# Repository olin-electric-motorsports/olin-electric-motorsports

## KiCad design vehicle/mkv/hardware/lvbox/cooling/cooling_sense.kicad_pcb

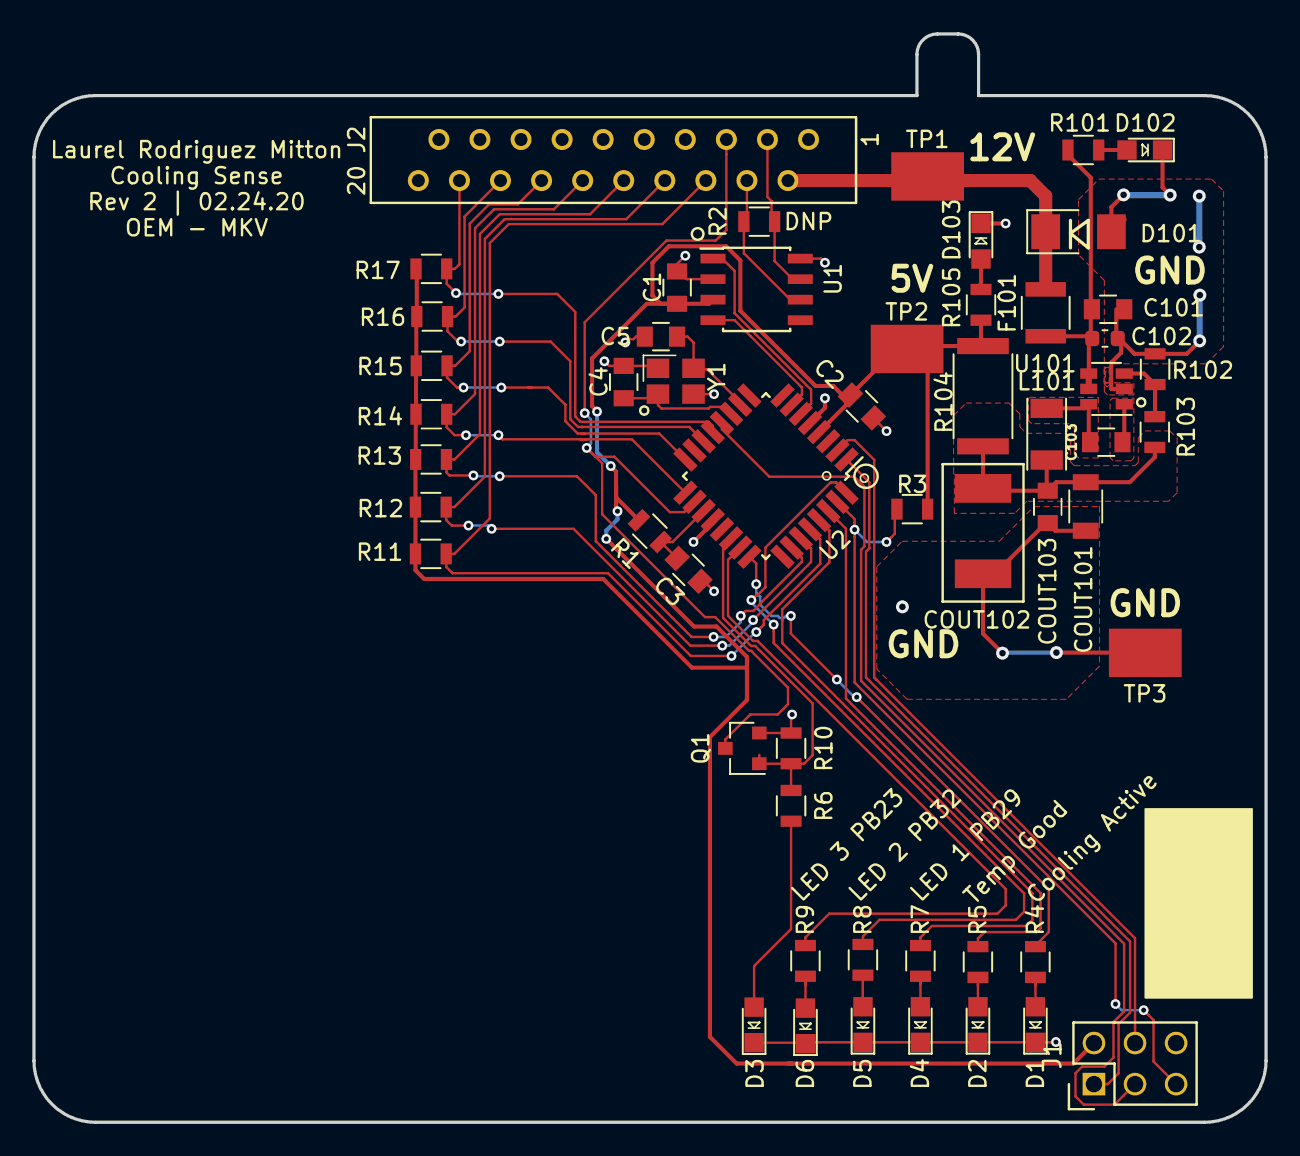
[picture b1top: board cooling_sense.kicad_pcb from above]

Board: 2 copper layers, 76.2 x 67.3 mm, 54 parts (0 on the bottom side), 41 nets.

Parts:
C1, C2, C101, C103: C_0.1uF; C_0805_OEM
C3: C_100pF; C_0805_OEM
C4, C5: C_30pF; C_0805_OEM
C102: C_2.2uF; C_0603_1608Metric
COUT101: C_22uF; C_1206_OEM
COUT102: C_33uF; Fuse_1812
COUT103: C_47uF; C_0805_OEM
D1, D2, D3, D4, D5, D6, D102, D103: LED_0805; LED_0805_OEM
D101: D_Zener_18V; DO-214AA
F101: F_500mA_16V; Fuse_1210
J1: CONN_02X03; Pin_Header_Straight_2x03
J2: MM_F_RA_20; micromatch_female_ra_20
L101: L_100uH; L_100uH_OEM
Q1: SSM3K333R; SOT-23F
R1: R_100; R_0805_OEM
R2: R_120_DNP; R_0805_OEM
R3, R10, R11, R12, R13, R14, R15, R16, R17: R_10K; R_0805_OEM
R4, R5, R6, R7, R8, R9, R101, R105: R_200; R_0805_OEM
R102: R_25K; R_0805_OEM
R103: R_100K; R_0805_OEM
R104: R_0_2512; R_2512_OEM
TP1, TP2, TP3: Test_Point_SMD
U1: MCP2561-E_SN; SOIC-8_3.9x4.9mm_Pitch1.27mm_OEM
U2: ATMEGA16M1; TQFP-32_7x7mm_Pitch0.8mm
U101: TPS560430YF; SOT-23-6_OEM
Y1: Crystal_SMD; Crystal_SMD_FA238

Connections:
/12V: D101.1, F101.2, J2.2, TP1.1
/CAN_HI: J2.3, R2.1, U1.7
/CAN_LO: J2.4, R2.2, U1.6
/CAN_RX: U1.4, U2.7
/CAN_TX: U1.1, U2.6
/COOLING_ACTIVE_LED: R4.1, U2.24
/LED_1: R7.1, U2.29
/LED_2: R8.1, U2.32
/LED_3: R9.1, U2.23
/MISO: J1.1, U2.1
/MOSI: J1.4, U2.2
/PUMP_CONTROL: Q1.1, R6.2, R10.2, U2.22
/PUMP_RELAY_READ: J2.5, Q1.3, U2.18
/READ_1: J2.6, R11.2, U2.28
/READ_2: J2.8, R12.2, U2.27
/READ_3: J2.10, R13.2, U2.26
/READ_4: J2.12, R14.2, U2.17
/READ_5: J2.14, R15.2, U2.16
/READ_6: J2.16, R16.2, U2.14
/READ_7: J2.18, R17.2, U2.13
/RESET: J1.5, R3.2, U2.31
/SCK: J1.3, U2.12
/TEMP_GOOD_LED: R5.1, U2.30
GND: C1.2, C2.2, C3.2, C4.2, C5.2, C101.2, C102.2, COUT101.2, COUT102.2, COUT103.2, D1.1, D2.1, D3.1, D4.1, D5.1, D6.1, D101.2, D102.1, D103.1, J1.6, J2.1, J2.7, J2.9, J2.11, J2.13, J2.15, J2.17, J2.19, J2.20, Q1.2, R10.1, R102.2, TP3.1, U1.2, U1.8, U2.5, U2.20, U101.2, Y1.2, Y1.4
unnamed: C3.1, R1.2, U2.19
unnamed: C4.1, U2.11, Y1.1
unnamed: C5.1, U2.10, Y1.3
unnamed: C101.1, C102.1, F101.1, R101.1, U101.4, U101.5
unnamed: C103.1, U101.1
unnamed: C103.2, L101.1, U101.6
unnamed: COUT101.1, COUT102.1, COUT103.1, L101.2, R103.1, R104.1
unnamed: D1.2, R4.2
unnamed: D2.2, R5.2
unnamed: D3.2, R6.1
unnamed: D4.2, R7.2
unnamed: D5.2, R8.2
unnamed: D6.2, R9.2
unnamed: D102.2, R101.2
unnamed: D103.2, R105.2
unnamed: R102.1, R103.2, U101.3
VCC: C1.1, C2.1, J1.2, R1.1, R3.1, R11.1, R12.1, R13.1, R14.1, R15.1, R16.1, R17.1, R104.2, R105.1, TP2.1, U1.3, U2.4

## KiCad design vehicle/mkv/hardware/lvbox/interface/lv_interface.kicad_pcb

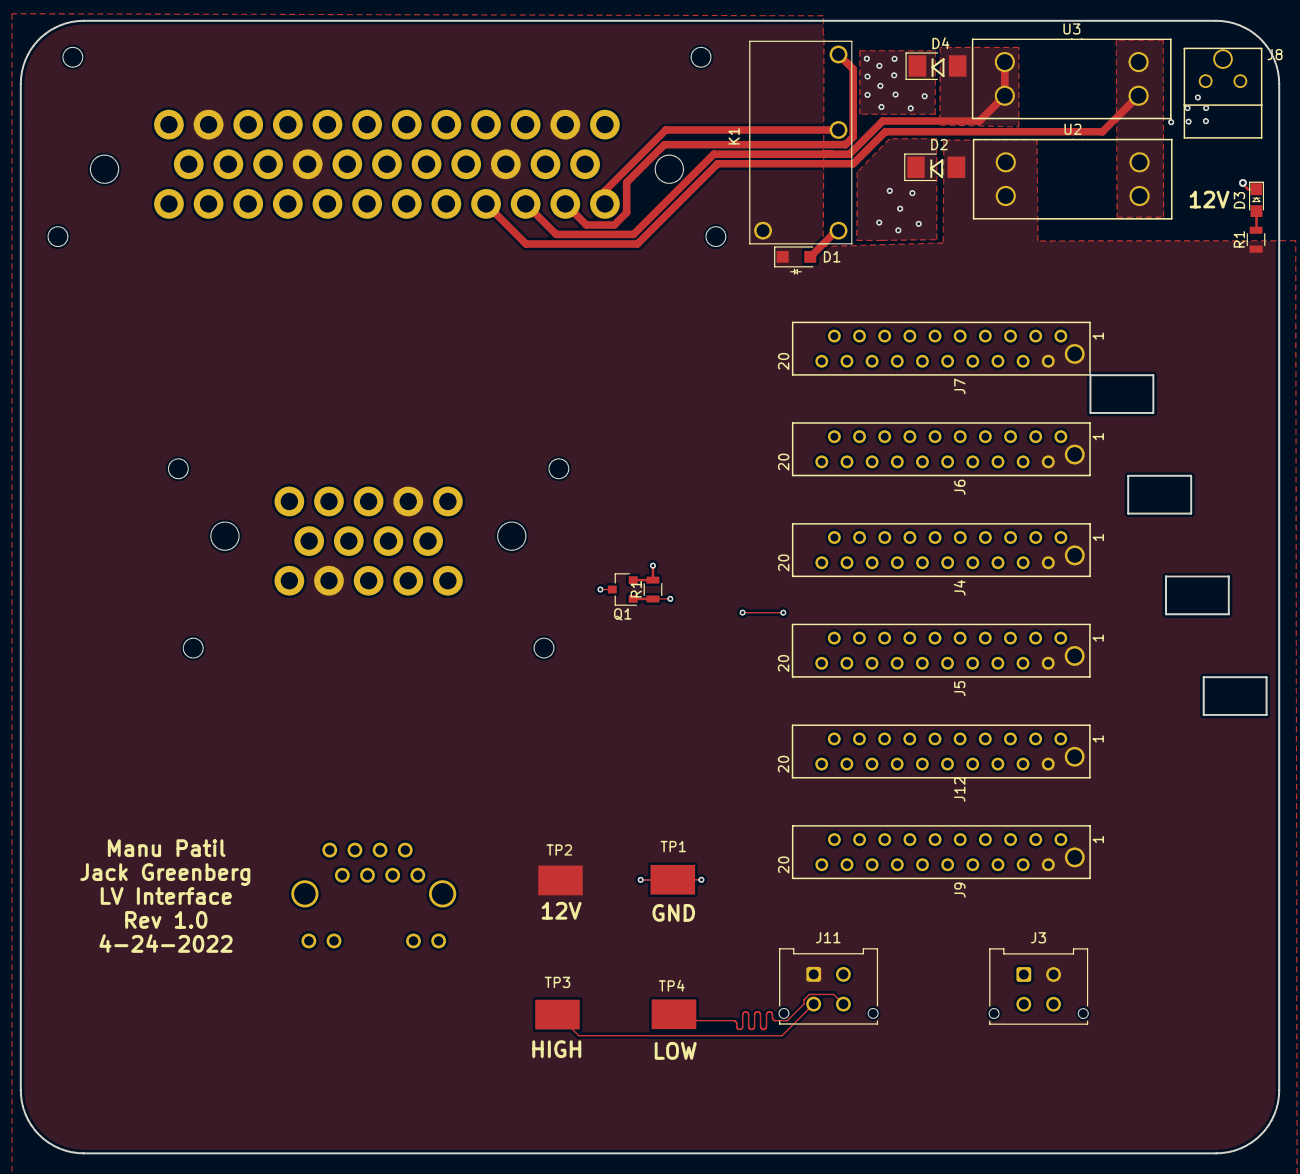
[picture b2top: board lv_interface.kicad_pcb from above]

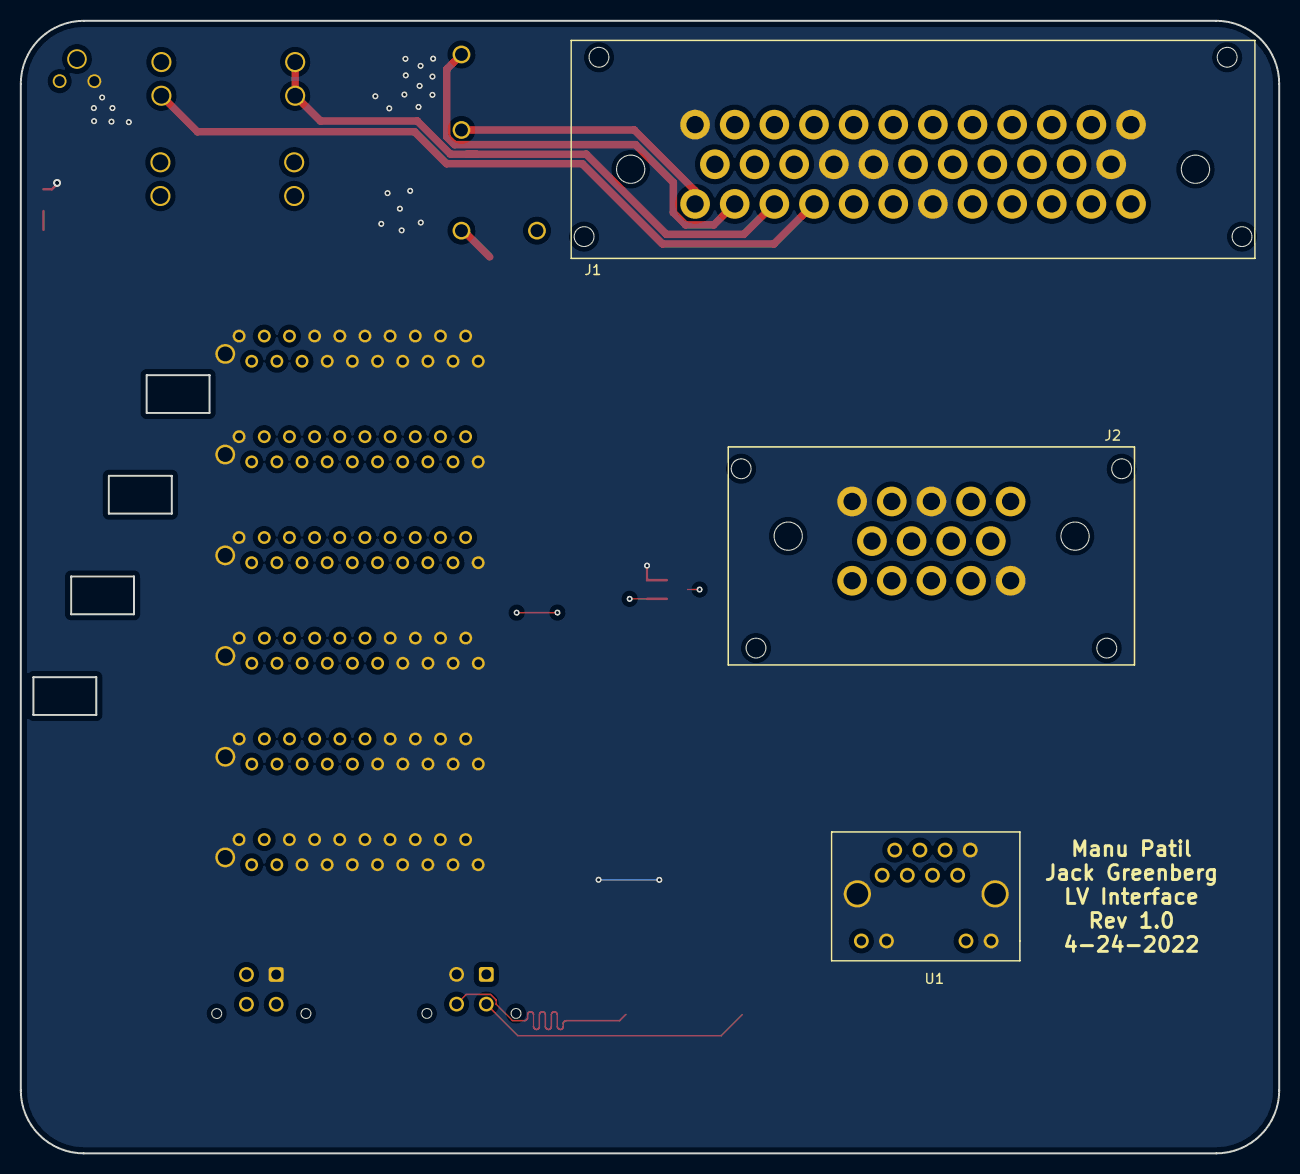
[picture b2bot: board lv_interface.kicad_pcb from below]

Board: 4 copper layers, 127.0 x 114.3 mm, 26 parts (3 on the bottom side), 46 nets.

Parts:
D1: SS110LW; D_SOD-123W_OEM
D2, D4: D_Zener_18V; DO-214AA
D3: LED_0805; LED_0805_OEM
J1: Ampseal_35_VT; Ampseal_35
J2: Ampseal_14_VT; Ampseal_14
J3, J11: MicroFit_VT_4
J4, J5, J6, J7, J9, J12: MM_M_VT_20; micromatch_female_vert_20
J8: UF_2_VT; Ultrafit_2
K1: G5Q-1A4-DC12; Relay_SPST_OMRON-G5Q-1A4_OEM
Q1: SSM3K333R; SOT-23F
R1: R_1K; R_0805_OEM
R1#2: R_10K; R_0805_OEM
TP1, TP2, TP3, TP4: Test_Point_SMD
U1: RJ45_VT; RJ45-Vertical
U2, U3: Fuse_Holder_Blade; Fuse_Block_Holder

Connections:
/5V: J2.5, J4.5, U1.7
/5V_GLV: J5.5, J12.5
/12V: D1.1, D2.2, J1.2, J1.11, J1.15, J1.20, J2.2, J2.13, J3.2, J4.2, J5.2, J6.2, J7.2, J9.2, J11.1, J12.2, K1.5, R1.1, TP2.1, U2.2
/BATT+: J1.28, J1.29, J8.1
/BRAKE PRESSURE +: J2.7, J4.10
/BRAKE PRESSURE -: J2.9, J4.12
/BRAKE PRESSURE SENSE: J2.8, J4.11
/BRAKELIGHT LSD: J2.3, J4.13
/BSPD > IS: J1.24, J4.18, K1.2
/BSPD CURRENT SENSE: J2.6, J4.19
/BSPD RELAY LSD: D1.2, J4.17, K1.1
/BSPD TEST SWITCH: J2.4, J4.14
/CAN +: J1.13, J1.21, J2.10, J3.3, J4.3, J5.3, J6.3, J7.3, J9.3, J11.3, J12.3, TP3.1, U1.2
/CAN -: J1.14, J1.22, J2.11, J3.4, J4.4, J5.4, J6.4, J7.4, J9.4, J11.4, J12.4, TP4.1, U1.1
/COOLING_PUMP: J1.31, Q1.3
/COOLING_PUMP_LSD: J4.16, Q1.1, R1#2.1
/CS_GLV: J5.10, J12.10
/E-STOP-R > BSPD: J1.25, J7.5, K1.3
/EXTRA TEMP 1 +: J1.3, J6.12
/EXTRA TEMP 1 -: J1.4, J6.13
/EXTRA TEMP 2 +: J1.5, J6.14
/EXTRA TEMP 2 -: J1.6, J6.15
/EXTRA TEMP 3 +: J1.7, J6.16
/EXTRA TEMP 3 -: J1.8, J6.17
/EXTRA TEMP 4 +: J1.9, J6.18
/EXTRA TEMP 4 -: J1.10, J6.19
/FUSE > E-STOP-L: D4.2, J1.26, J7.6, U3.2
/GLVMS>FUSE: J1.27, U2.1, U3.1
/MC TEMP +: J1.34, J6.10
/MC TEMP -: J1.35, J6.11
/MISO: J4.6, U1.5
/MISO_GLV: J5.8, J12.8
/MOSI: J4.7, U1.6
/MOSI_GLV: J5.9, J12.9
/MOTOR TEMP +: J1.32, J6.8
/MOTOR TEMP -: J1.33, J6.9
/RADIATOR TEMP +: J1.18, J6.6
/RADIATOR TEMP -: J1.19, J6.7
/RESET: J4.9, U1.3
/RJ45 LED G: J4.15, U1.12
/SCK: J4.8, U1.4
/SCK_GLV: J5.11, J12.11
/SCL_GLV: J5.7, J12.7
/SDA_GLV: J5.6, J12.6
GND: D2.1, D3.1, D4.1, J1.1, J1.12, J1.16, J1.17, J1.23, J1.30, J2.1, J2.12, J2.14, J3.1, J4.1, J4.20, J5.1, J5.13, J5.14, J5.15, J5.16, J5.17, J5.18, J5.19, J5.20, J6.1, J6.20, J7.1, J7.7, J7.8, J7.9, J7.10, J7.11, J7.12, J7.13, J7.14, J7.15, J7.16, J7.17, J7.18, J7.19, J7.20, J8.2, J9.1, J9.5, J9.6, J9.7, J9.8, J9.9, J9.10, J9.11, J9.12, J9.13, J9.14, J9.15, J9.16, J9.17, J9.18, J9.19, J9.20, J11.2, J12.1, J12.12, J12.13, J12.14, J12.15, J12.16, J12.17, J12.18, J12.19, J12.20, Q1.2, R1#2.2, TP1.1, U1.8, U1.9, U1.11, U1.13, U1.14
unnamed: D3.2, R1.2

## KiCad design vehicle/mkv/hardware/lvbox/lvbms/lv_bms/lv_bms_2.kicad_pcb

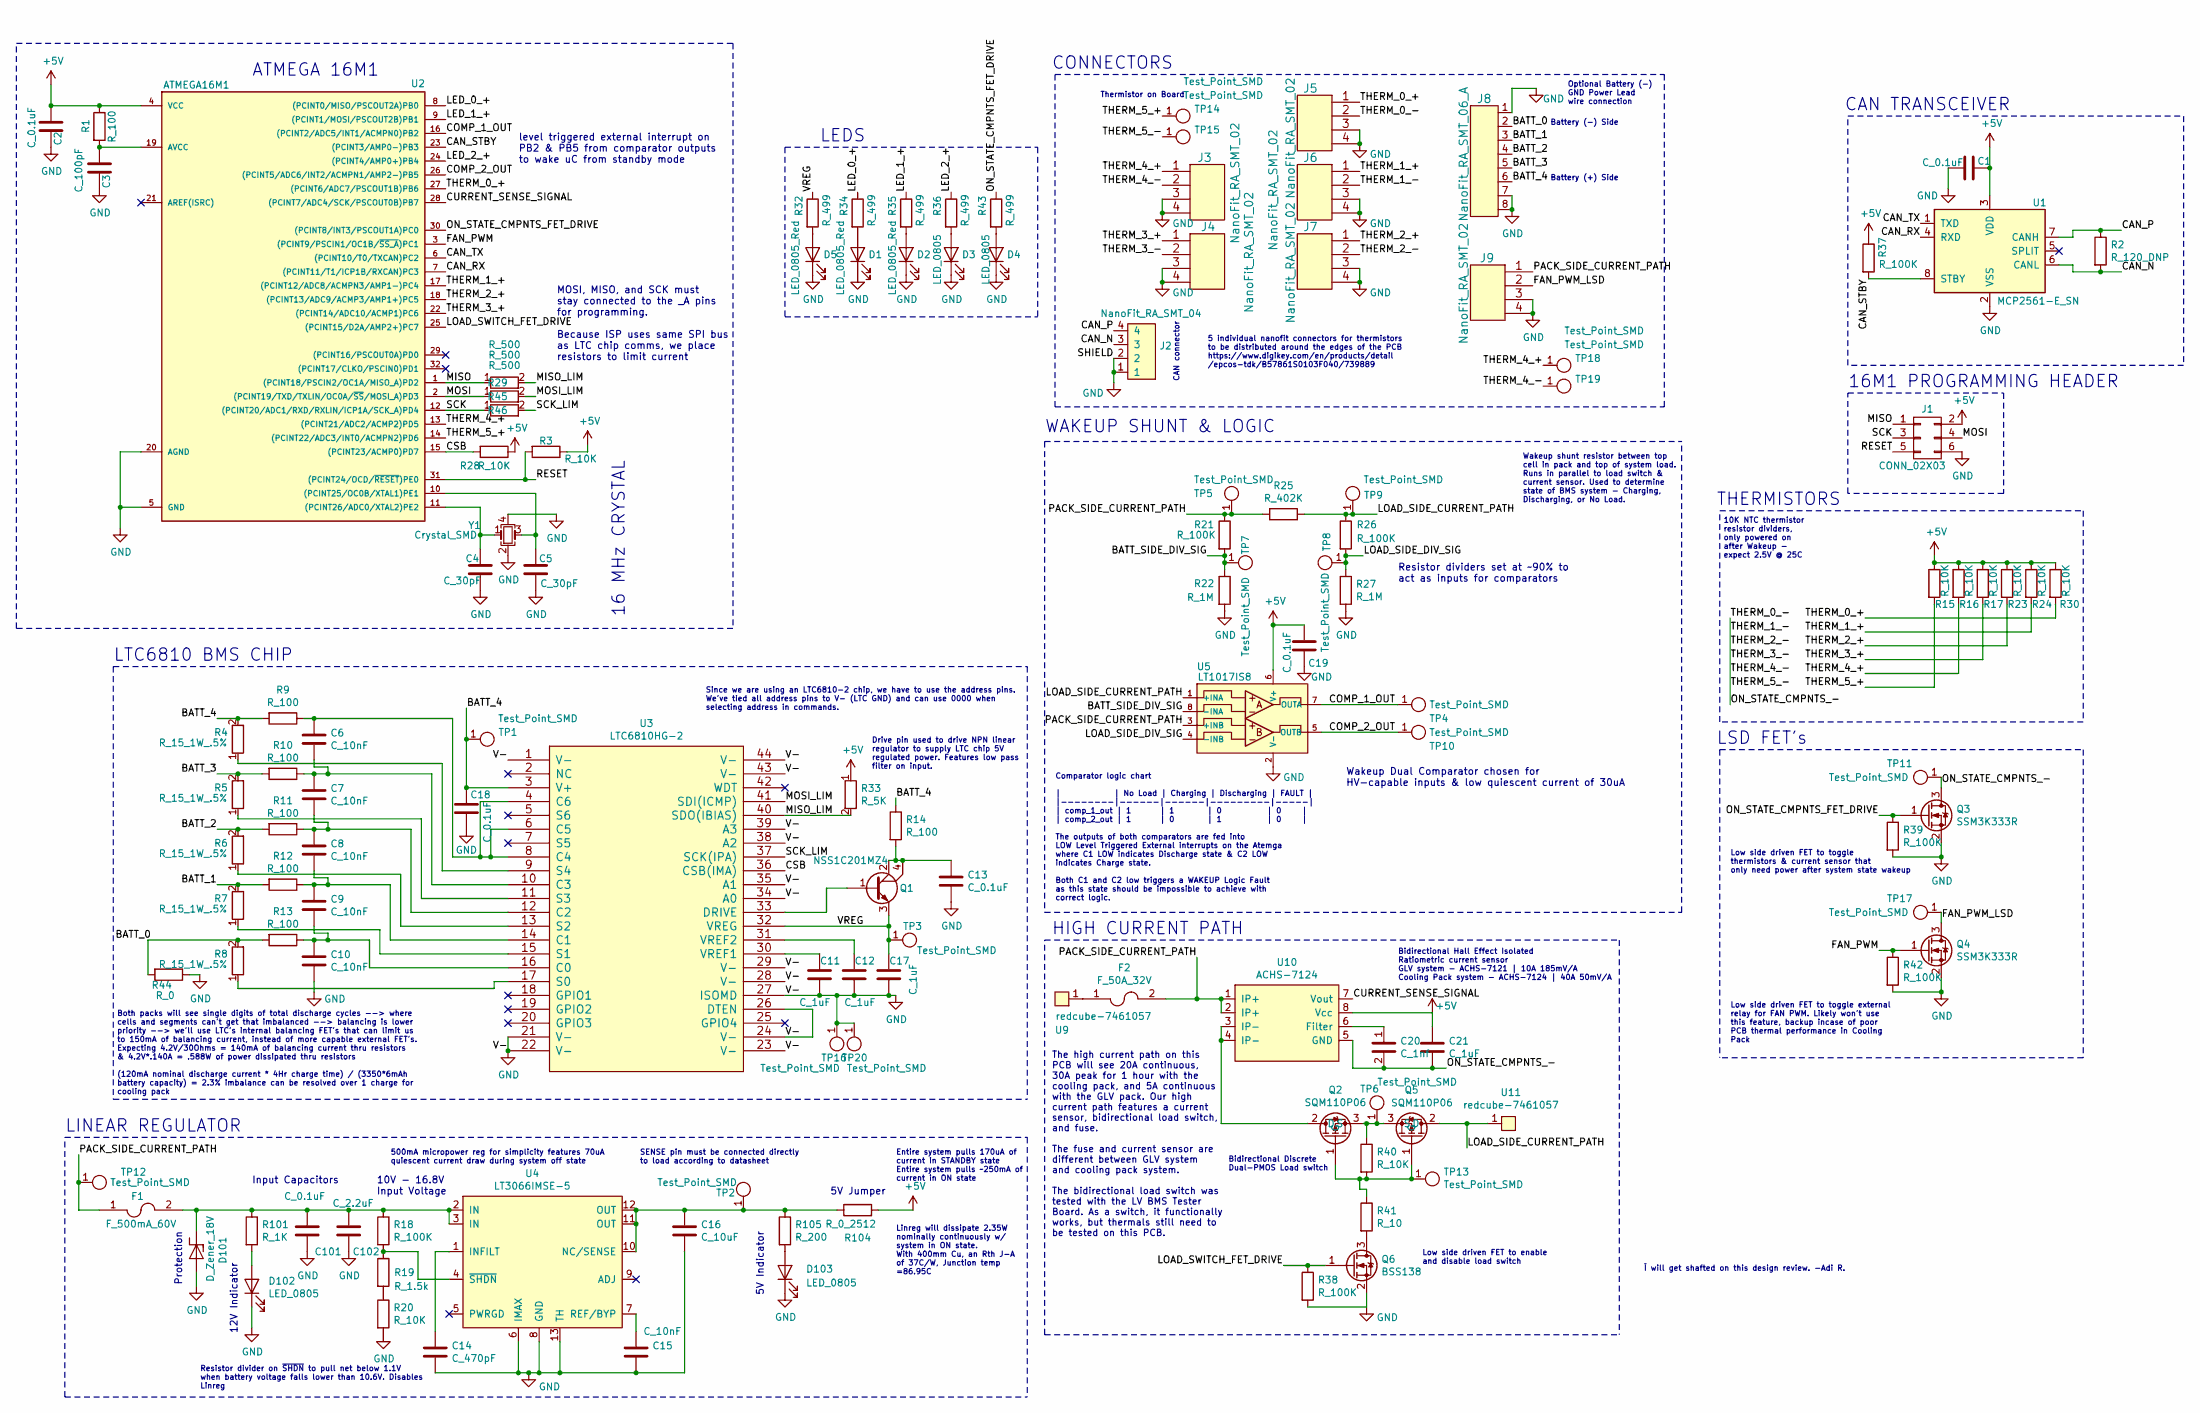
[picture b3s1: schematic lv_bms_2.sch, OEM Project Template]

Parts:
C1, C2, C13, C18, C19, C101: C_0.1uF; C_0805_OEM; MPN 478-3352-1-ND
C3: C_100pF; C_0805_OEM; MPN 732-7852-1-ND
C4, C5: C_30pF; C_0805_OEM; MPN 1276-1130-1-ND
C6, C7, C8, C9, C10, C15: C_10nF; C_0805_OEM; MPN C1206C103KCRACTU
C11, C12, C17, C21: C_1uF; C_0805_OEM
C14: C_470pF; C_0805_OEM
C16: C_10uF; C_0805_OEM; MPN 1276-1052-1-ND
C20: C_1nf; C_0805_OEM
C102: C_2.2uF; C_0805_OEM; MPN 311-1451-1-ND
D1, D2, D5: LED_0805_Red; LED_0805_OEM; MPN 475-1415-1-ND
D3, D4, D102, D103: LED_0805; LED_0805_OEM; MPN 475-1410-1-ND
D101: D_Zener_18V; DO-214AA; MPN SMBJ5355B-TPMSCT-ND
F1: F_500mA_60V; Fuse_1812_4532Metric; MPN 1812L050/60MR-A
F2: F_50A_32V; Fuse_1206; MPN 0685P9500-01
J1: CONN_02X03; Pin_Header_Straight_2x03; MPN 609-3234-ND
J2: NanoFit_RA_SMT_04
J3, J4, J5, J6, J7, J9: NanoFit_RA_SMT_02; MPN 1054301102
J8: NanoFit_RA_SMT_06_A; NanoFit_RA_SMT_06; MPN 1054302106
Q1: NSS1C201MZ4; SOT-223; MPN NSS1C201MZ4T3GOSCT-ND
Q2, Q5: SQM110P06; TO-263-3-TabPin2; MPN SQM110P06-8m9L
Q3, Q4: SSM3K333R; SOT-23F; MPN SSM3K333RLFCT-ND
Q6: BSS138; SOT-23
R1, R9, R10, R11, R12, R13, R14: R_100; R_0805_OEM; MPN RNCP0805FTD100RCT-ND
R2: R_120_DNP; R_0805_OEM; MPN 667-ERJ-6ENF1200V
R3, R15, R16, R17, R20, R23, R24, R28, R30, R40: R_10K; R_0805_OEM; MPN CRS0805-FX-1002ELFCT-ND
R4, R5, R6, R7, R8: R_15_1W_.5%; Fuse_1206; MPN HRG3216Q-15R0-D-T1
R18, R21, R26, R37, R38, R39, R42: R_100K; R_0805_OEM; MPN P100KCCT-ND
R19: R_1.5k; R_0805_OEM; MPN CRCW20101K50FKEF
R22, R27: R_1M; R_0805_OEM; MPN RMCF0805JT1M00CT-ND
R25: R_402K; R_0805_OEM; MPN RMCF0805FT402KCT-ND
R29, R45, R46: R_500; R_0805_OEM
R32, R34, R35, R36, R43: R_499; R_0805_OEM; MPN P499CCT-ND
R33: R_5K; R_0805_OEM
R41: R_10; R_0805_OEM; MPN ERJ-P06F10R0V
R44: R_0; R_0603_1608Metric; MPN P0.0GCT-ND
R101: R_1K; R_0805_OEM; MPN RNCP0805FTD1K00CT-ND
R104: R_0_2512; R_2512_OEM; MPN A121322CT-ND
R105: R_200; R_0805_OEM; MPN RMCF0805JT200RCT-ND
TP1, TP2, TP3, TP4, TP5, TP6, TP7, TP8, TP9, TP10, TP11, TP12, TP13, TP14, TP15, TP17, TP18, TP19: Test_Point_SMD; TestPoint_Pad_D1.5mm
TP16, TP20: Test_Point_SMD
U1: MCP2561-E_SN; SOIC-8_3.9x4.9mm_Pitch1.27mm_OEM; MPN MCP2561-E/SN-ND
U2: ATMEGA16M1; TQFP-32_7x7mm_Pitch0.8mm; MPN ATMEGA16M1-AU-ND
U3: LTC6810HG-2; SOP50P780X200-44N
U4: LT3066IMSE-5; MSOP-12_MSE; MPN LT3066IMSE-5#PBF
U5: LT1017IS8; SO-8_S; MPN lt1017is8#pbf
U9, U11: redcube-7461057; redcube_pressfit_6pin; MPN 7461057
U10: ACHS-7124; OPTO_HCPL-070A-000E; MPN ACHS-7124-000E
Y1: Crystal_SMD; Crystal_SMD_FA238; MPN 887-1125-1-ND

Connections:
+5V: C1.1, C2.1, C19.1, C21.1, J1.2, R1.1, R3.1, R15.1, R16.1, R17.1, R23.1, R24.1, R28.1, R30.1, R33.1, R37.1, R104.2, U1.3 (VDD), U2.4 (VCC), U5.6 (V+), U10.8 (Vcc)
/BATT_0: J8.2, R8.2, R13.2, R44.2
/BATT_1: J8.3, R7.2, R12.2
/BATT_2: J8.4, R6.2, R11.2
/BATT_3: J8.5, R5.2, R10.2
/BATT_4: C18.2, J8.6, R4.2, R9.2, R14.1, TP1.1, U3.3 (V+)
/BATT_SIDE_DIV_SIG: R21.2, R22.1, TP7.1, U5.8 (-INA)
/CAN_N: J2.3, R2.2, U1.6 (CANL)
/CAN_P: J2.4, R2.1, U1.7 (CANH)
/CAN_RX: U1.4 (RXD), U2.7 ((PCINT11/T1/ICP1B/RXCAN)PC3)
/CAN_STBY: R37.2, U1.8 (STBY), U2.23 ((PCINT3/AMP0-)PB3)
/CAN_TX: U1.1 (TXD), U2.6 ((PCINT10/T0/TXCAN)PC2)
/COMP_1_OUT: TP4.1, U2.16 ((PCINT2/ADC5/INT1/ACMPN0)PB2), U5.7 (OUTA)
/COMP_2_OUT: TP10.1, U2.26 ((PCINT5/ADC6/INT2/ACMPN1/AMP2-)PB5), U5.5 (OUTB)
/CSB: R28.2, U2.15 ((PCINT23/ACMP0)PD7), U3.36 (CSB(IMA))
/CURRENT_SENSE_SIGNAL: U2.28 ((PCINT7/ADC4/SCK/PSCOUT0B)PB7), U10.7 (Vout)
/FAN_PWM: Q4.1 (G), R42.1, U2.3 ((PCINT9/PSCIN1/OC1B/~SS_A~)PC1)
/FAN_PWM_LSD: J9.2, Q4.3 (D), TP17.1
/LED_0_+: R34.1, U2.8 ((PCINT0/MISO/PSCOUT2A)PB0)
/LED_1_+: R35.1, U2.9 ((PCINT1/MOSI/PSCOUT2B)PB1)
/LED_2_+: R36.1, U2.24 ((PCINT4/AMP0+)PB4)
/LOAD_SIDE_CURRENT_PATH: Q5.2 (D), R25.1, R26.1, TP9.1, U5.1 (+INA), U11.1
/LOAD_SIDE_DIV_SIG: R26.2, R27.1, TP8.1, U5.4 (-INB)
/LOAD_SWITCH_FET_DRIVE: Q6.1 (G), R38.1, U2.25 ((PCINT15/D2A/AMP2+)PC7)
/MISO: J1.1, R29.1, U2.1 ((PCINT18/PSCIN2/OC1A/MISO_A)PD2)
/MISO_LIM: R29.2, R33.2, U3.40 (SDO(IBIAS))
/MOSI: J1.4, R45.1, U2.2 ((PCINT19/TXD/TXLIN/OC0A/~SS~/MOSI_A)PD3)
/MOSI_LIM: R45.2, U3.41 (SDI(ICMP))
/ON_STATE_CMPNTS_-: C20.2, C21.2, J3.2, J4.2, J5.2, J6.2, J7.2, Q3.3 (D), TP11.1, TP15.1, TP19.1, U10.5 (GND)
/ON_STATE_CMPNTS_FET_DRIVE: Q3.1 (G), R39.1, R43.1, U2.30 ((PCINT8/INT3/PSCOUT1A)PC0)
/PACK_SIDE_CURRENT_PATH: F1.1, F2.2, J9.1, R21.1, R25.2, TP5.1, TP12.1, U5.3 (+INB), U10.1 (IP+), U10.2 (IP+)
/RESET: J1.5, R3.2, U2.31 ((PCINT24/OCD/~RESET~)PE0)
/SCK: J1.3, R46.1, U2.12 ((PCINT20/ADC1/RXD/RXLIN/ICP1A/SCK_A)PD4)
/SCK_LIM: R46.2, U3.37 (SCK(IPA))
/THERM_0_+: J5.1, R30.2, U2.27 ((PCINT6/ADC7/PSCOUT1B)PB6)
/THERM_1_+: J6.1, R24.2, U2.17 ((PCINT12/ADC8/ACMPN3/AMP1-)PC4)
/THERM_2_+: J7.1, R23.2, U2.18 ((PCINT13/ADC9/ACMP3/AMP1+)PC5)
/THERM_3_+: J4.1, R17.2, U2.22 ((PCINT14/ADC10/ACMP1)PC6)
/THERM_4_+: J3.1, R16.2, TP18.1, U2.13 ((PCINT21/ADC2/ACMP2)PD5)
/THERM_5_+: R15.2, TP14.1, U2.14 ((PCINT22/ADC3/INT0/ACMPN2)PD6)
/VREG: C17.1, Q1.3, R32.1, TP3.1, U3.32 (VREG)
GND: C1.2, C2.2, C3.2, C4.2, C5.2, C10.2, C11.2, C12.2, C13.2, C14.2, C15.2, C16.2, C17.2, C18.1, C19.2, C101.2, C102.2, D1.1 (K), D2.1 (K), D3.1 (K), D4.1 (K), D5.1 (K), D101.2 (A), D102.1 (K), D103.1 (K), J1.6, J2.1, J2.2, J3.3, J3.4, J4.3, J4.4, J5.3, J5.4, J6.3, J6.4, J7.3, J7.4, J8.1, J8.7, J8.8, J9.3, J9.4, Q3.2 (S), Q4.2 (S), Q6.2 (S), R20.2, R22.2, R27.2, R38.2, R39.2, R42.2, R44.1, TP16.1, TP20.1, U1.2 (VSS), U2.5 (GND), U2.20 (AGND), U3.1 (V-), U3.21 (V-), U3.22 (V-), U3.23 (V-), U3.24 (V-), U3.26 (DTEN), U3.27 (ISOMD), U3.28 (V-), U3.29 (V-), U3.34 (A0), U3.35 (A1), U3.38 (A2), U3.39 (A3), U3.43 (V-), U3.44 (V-), U4.6 (IMAX), U4.8 (GND), U4.13 (TH), U5.2 (V-), Y1.2, Y1.4
unnamed: C3.1, R1.2, U2.19 (AVCC)
unnamed: C4.1, U2.11 ((PCINT26/ADC0/XTAL2)PE2), Y1.1
unnamed: C5.1, U2.10 ((PCINT25/OC0B/XTAL1)PE1), Y1.3
unnamed: C6.1, R9.1, U3.4 (C6), U3.6 (C5), U3.8 (C4)
unnamed: C6.2, C7.1, R10.1, U3.10 (C3)
unnamed: C7.2, C8.1, R11.1, U3.12 (C2)
unnamed: C8.2, C9.1, R12.1, U3.14 (C1)
unnamed: C9.2, C10.1, R13.1, U3.16 (C0)
unnamed: C11.1, U3.30 (VREF1)
unnamed: C12.1, U3.31 (VREF2)
unnamed: C13.1, Q1.2, Q1.4, R14.2
unnamed: C14.1, U4.1 (INFILT)
unnamed: C15.1, U4.7 (REF/BYP)
unnamed: C16.1, R104.1, R105.1, TP2.1, U4.10 (NC/SENSE), U4.11 (OUT), U4.12 (OUT)
unnamed: C20.1, U10.6 (Filter)
unnamed: C101.1, C102.1, D101.1 (K), F1.2, R18.1, R101.1, U4.2 (IN), U4.3 (IN)
unnamed: D1.2 (A), R34.2
unnamed: D2.2 (A), R35.2
unnamed: D3.2 (A), R36.2
unnamed: D4.2 (A), R43.2
unnamed: D5.2 (A), R32.2
unnamed: D102.2 (A), R101.2
unnamed: D103.2 (A), R105.2
unnamed: F2.1, U9.1
unnamed: Q1.1, U3.33 (DRIVE)
unnamed: Q2.1 (G), Q5.1 (G), R40.2, R41.1, TP13.1
unnamed: Q2.2 (D), U10.3 (IP-), U10.4 (IP-)
unnamed: Q2.3 (S), Q5.3 (S), R40.1, TP6.1
unnamed: Q6.3 (D), R41.2
unnamed: R4.1, U3.9 (S4)
unnamed: R5.1, U3.11 (S3)
unnamed: R6.1, U3.13 (S2)
unnamed: R7.1, U3.15 (S1)
unnamed: R8.1, U3.17 (S0)
unnamed: R18.2, R19.1, U4.4 (~SHDN)
unnamed: R19.2, R20.1

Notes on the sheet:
Input Capacitors
12V Indicator
Protection
LINEAR REGULATOR
5V Indicator
CAN TRANSCEIVER
ATMEGA 16M1
16 MHz CRYSTAL
16M1 PROGRAMMING HEADER
Comparator logic chart | | No Load | Charging | Discharging | FAULT | |--------|------|------|---------|-----| | comp_1_out | 1 | 1 | 0 | 0 | | comp_2_out | 1 | 0 | 1 | 0 | The outputs of both comparators are fed into LOW Level Triggered External interrupts on the Atemga where C1 LOW indicates Disc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
level triggered external interrupt on PB2 & PB5 from comparator outputs to wake uC from standby mode
CONNECTORS
WAKEUP SHUNT & LOGIC
LEDS
LTC6810 BMS CHIP
500mA micropower reg for simplicity features 70uA quiescent current draw during system off state
Wakeup shunt resistor between top cell in pack and top of system load. Runs in parallel to load switch & current sensor. Used to determine state of BMS system - Charging, Discharging, or No Load.
Wakeup Dual Comparator chosen for HV-capable inputs & low quiescent current of 30uA
Resistor divider on ~SHDN~ to pull net below 1.1V when battery voltage falls lower than 10.6V. Disables Linreg
SENSE pin must be connected directly to load according to datasheet
LSD FET's
THERMISTORS
Drive pin used to drive NPN linear regulator to supply LTC chip 5V regulated power. Features low pass filter on input.
10K NTC thermistor resistor dividers, only powered on after Wakeup - expect 2.5V @ 25C
5 individual nanofit connectors for thermistors to be distributed around the edges of the PCB https://www.digikey.com/en/products/detail /epcos-tdk/B57861S0103F040/739889
Low side driven FET to toggle thermistors & current sensor that only need power after system state wakeup
~I will get shafted on this design review.~ -Adi R.
Bidirectional Hall Effect Isolated Ratiometric current sensor GLV system - ACHS-7121 | 10A 185mV/A Cooling Pack system - ACHS-7124 | 40A 50mV/A
Both packs will see single digits of total discharge cycles --> where cells and segments can't get that imbalanced --> balancing is lower priority --> we'll use LTC's internal balancing FET's that can limit us to 150mA of balancing current, instead of more capable external FET's. Expecting 4.2V/30O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
Battery (-) Side
Battery (+) Side
Entire system pulls 170uA of current in STANDBY state Entire system pulls ~~250mA of current in ON state
CAN connector
5V Jumper
Low side driven FET to enable and disable load switch
HIGH CURRENT PATH
Bidirectional Discrete Dual-PMOS Load switch
Thermistor on Board
Since we are using an LTC6810-2 chip, we have to use the address pins. We've tied all address pins to V- (LTC GND) and can use 0000 when selecting address in commands.
MOSI, MISO, and SCK must stay connected to the _A pins for programming. Because ISP uses same SPI bus as LTC chip comms, we place resistors to limit current

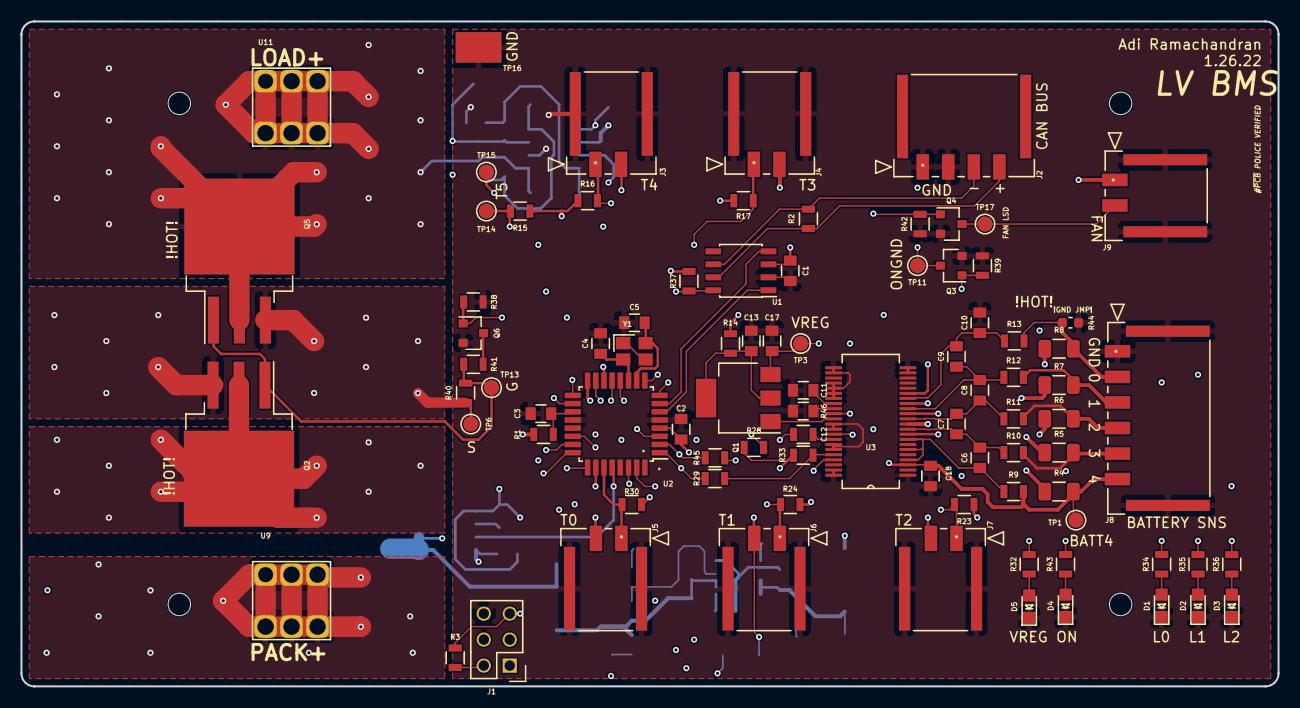
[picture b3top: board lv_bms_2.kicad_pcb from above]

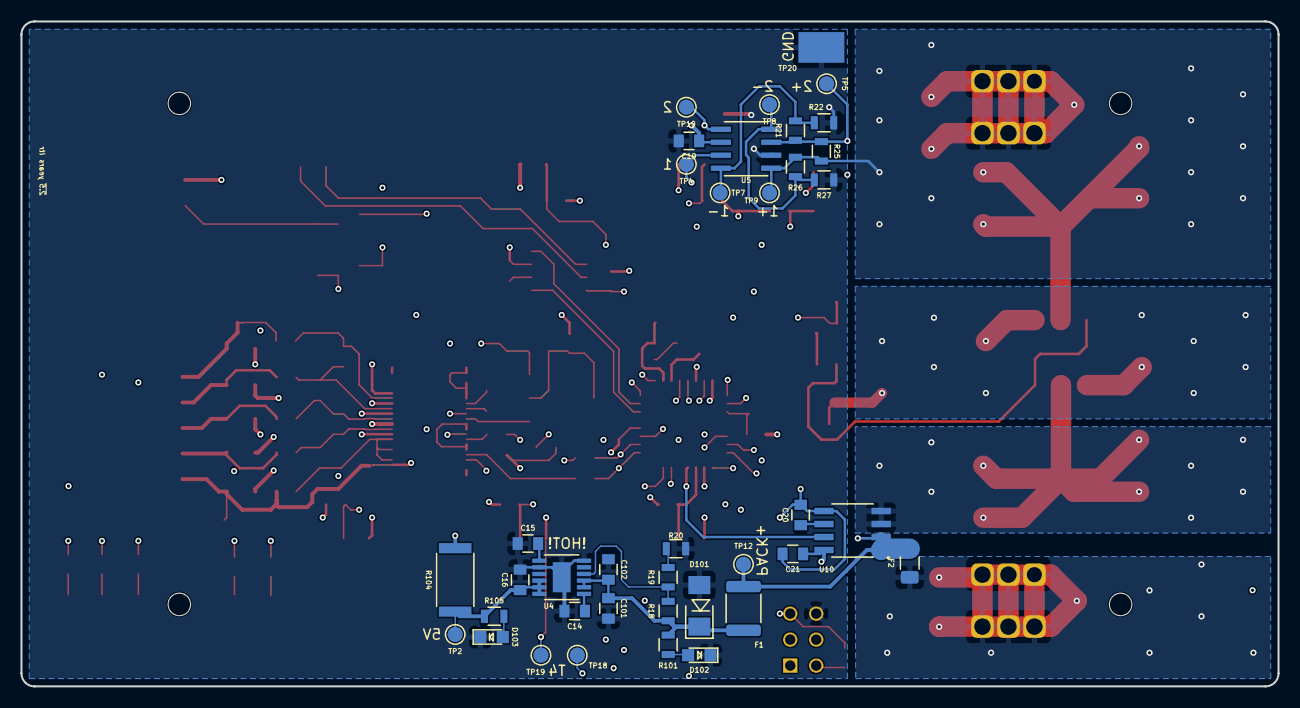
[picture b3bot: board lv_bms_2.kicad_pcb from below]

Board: 4 copper layers, 122.9 x 65.0 mm, 125 parts (38 on the bottom side), 78 nets.

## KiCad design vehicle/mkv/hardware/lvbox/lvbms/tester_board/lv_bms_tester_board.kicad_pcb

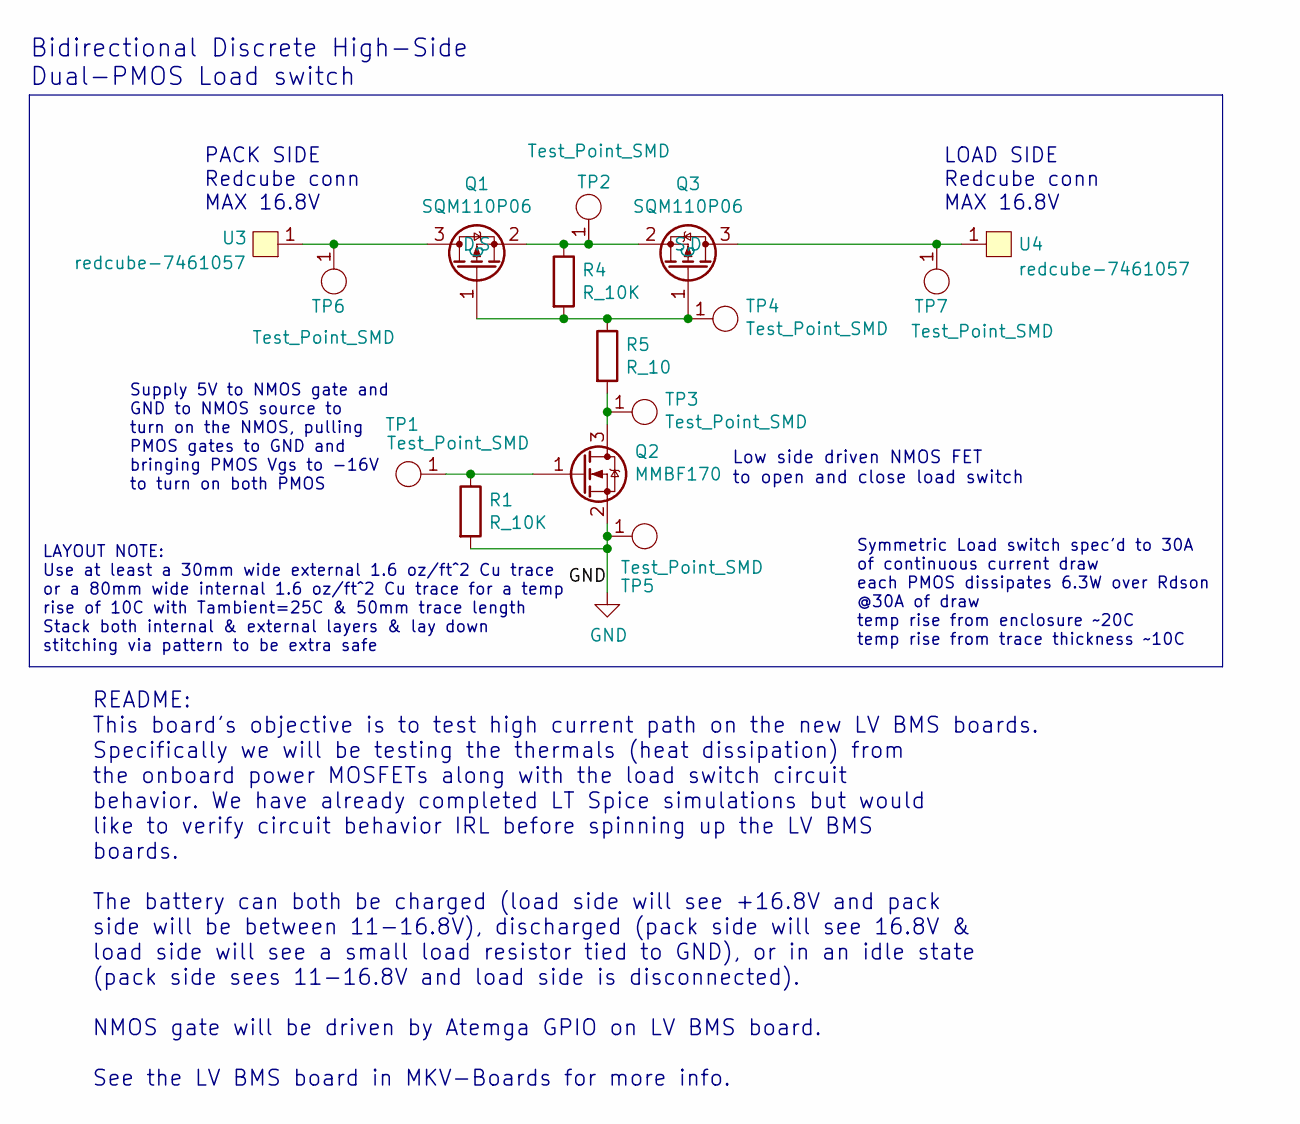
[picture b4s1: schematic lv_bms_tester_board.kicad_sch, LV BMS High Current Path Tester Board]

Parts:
Q1, Q3: SQM110P06; TO-263-3-TabPin2; MPN SQM110P06-8m9L
Q2: MMBF170; SOT-23-3_OEM; MPN MMBF170CT-ND
R1, R4: R_10K; R_0805_OEM; MPN CRS0805-FX-1002ELFCT-ND
R5: R_10; R_0805_OEM; MPN ERJ-P06F10R0V
TP1, TP5, TP6, TP7: Test_Point_SMD
TP2, TP3, TP4: Test_Point_SMD; TestPoint_Pad_D1.5mm
U3, U4: redcube-7461057; redcube_pressfit_6pin; MPN 7461057

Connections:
GND: Q2.2 (S), R1.2, TP5.1
unnamed: Q1.1 (G), Q3.1 (G), R4.2, R5.1, TP4.1
unnamed: Q1.2 (S), Q3.2 (S), R4.1, TP2.1
unnamed: Q1.3 (D), TP6.1, U3.1
unnamed: Q2.1 (G), R1.1, TP1.1
unnamed: Q2.3 (D), R5.2, TP3.1
unnamed: Q3.3 (D), TP7.1, U4.1

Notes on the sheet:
Supply 5V to NMOS gate and GND to NMOS source to turn on the NMOS, pulling PMOS gates to GND and bringing PMOS Vgs to -16V to turn on both PMOS
LAYOUT NOTE: Use at least a 30mm wide external 1.6 oz/ft^2 Cu trace or a 80mm wide internal 1.6 oz/ft^2 Cu trace for a temp rise of 10C with Tambient=25C & 50mm trace length Stack both internal & external layers & lay down stitching via pattern to be extra safe
README: This board's objective is to test high current path on the new LV BMS boards. Specifically we will be testing the thermals (heat dissipation) from the onboard power MOSFETs along with the load switch circuit behavior. We have already completed LT Spice simulations but would like to verify c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
Symmetric Load switch spec'd to 30A of continuous current draw each PMOS dissipates 6.3W over Rdson @30A of draw temp rise from enclosure ~20C temp rise from trace thickness ~10C
Low side driven NMOS FET to open and close load switch
PACK SIDE Redcube conn MAX 16.8V
LOAD SIDE Redcube conn MAX 16.8V
Bidirectional Discrete High-Side Dual-PMOS Load switch

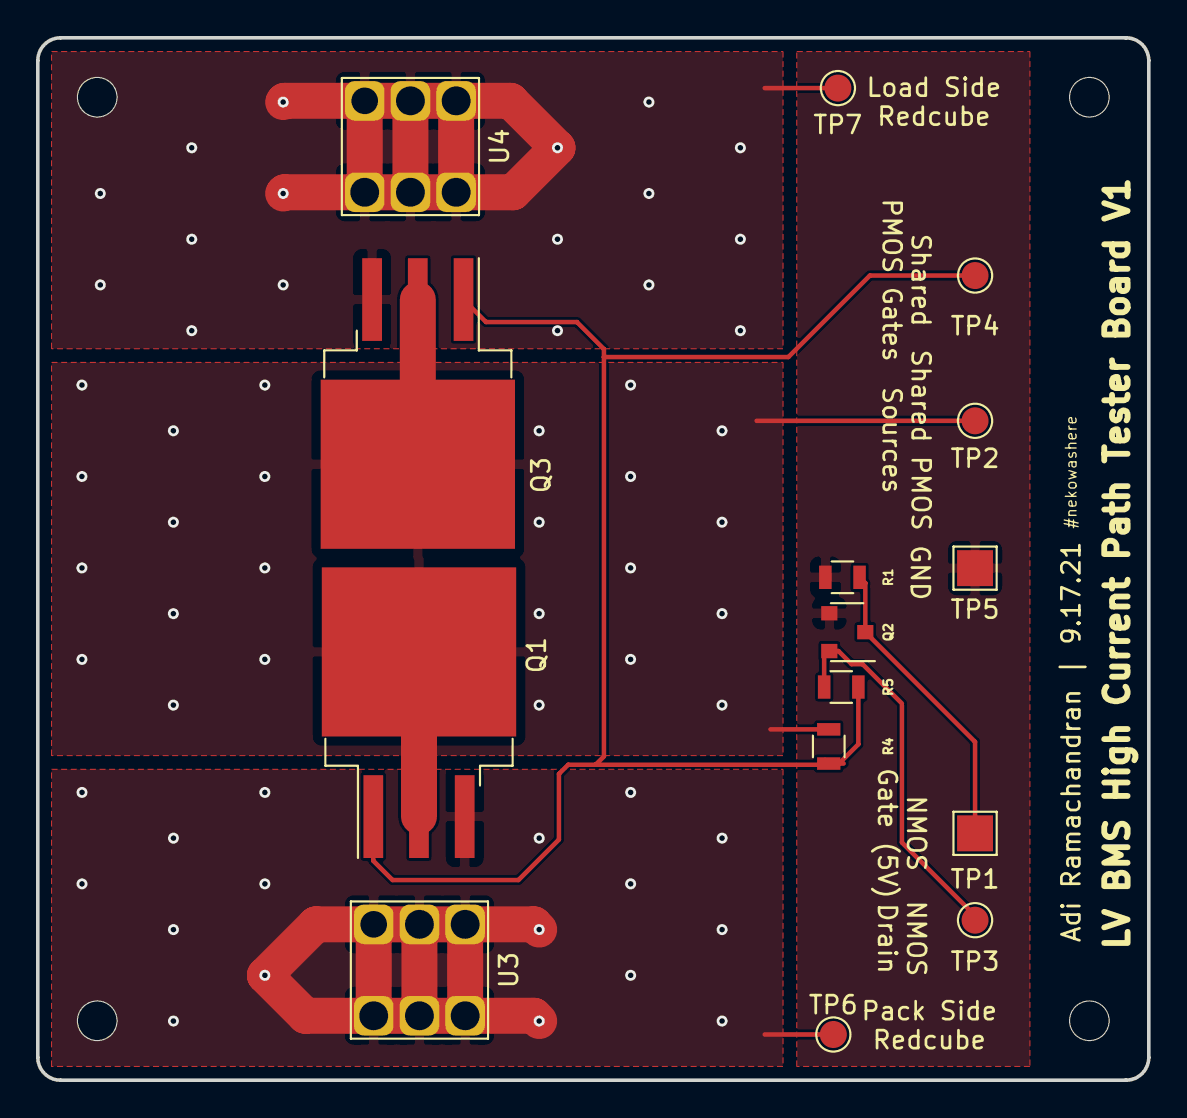
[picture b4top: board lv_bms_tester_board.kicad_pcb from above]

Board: 4 copper layers, 61.7 x 57.9 mm, 15 parts (0 on the bottom side), 7 nets.

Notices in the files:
parts and their libraries:
Copyright 2016 Accelerated Designs. All rights reserved.
